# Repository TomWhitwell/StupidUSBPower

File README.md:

# StupidUSBPower

This is a USB Stick Eurorack Power supply. 

- It takes +5v from USB power, and turns it into +/-12v and also passes along the 5v. 
- The key component is a IR0512S DC-DC Converter from XP Power which [costs about £8.50 from Farnell](http://uk.farnell.com/xp-power/ir0512s/dc-dc-converter-semi-reg-dual/dp/1860988) and gives 125mA of power on both rails.  This is a standard SIP package, so other dual output DC-DC converters may work in the same spot. I just chose the one with a good output. 
- The board also includes a simple passive headphone output; the 3.5mm mono socket goes through a 50k Volume Pot into the stereo headphone socket. This didn't work well with three-connector iphone earbuds, but was fine with normal stereo headphones. 
- Seems to work well with portable USB batteries. 
- The IR0512S is rated 125mA on +12v and -12v, but that seems quite conservative. The Dixie+Turing+Radio Music in the photo below ran quite happily, with an expected current draw of 160mA on +12v, 52mA on -12v. The converter module was warm but certainly not hot. The whole thing was drawing 600mA from the USB port. 

## Updates 
- This project has taken off a little bit! [C1T1ZEN](https://www.instagram.com/p/BEDGNGCOpEv/?taken-by=c1t1zen) has been building incredibly cool lunchbox euro boxes powered with his improved version. 
- Just got a [Re:Load2](http://www.arachnidlabs.com/reload-2/) so I've been trying to destroy my USB power prototype. With the IR0512S...
    - 250ma on +12v: Seems to work quite happily, pulling 710ma from the USB port. 
    - 350ma: It appears to work OK. The lights are on, but I'm making no no claims on the power stability, ripple etc, pulling about 1amp from USB, the converter is definitely HOT, but ran for an afternoon without death. 
    - 460ma: Seems to be the absolute max. Really hot. Above that, when you try to pull more current, all the lights blink and it says goodbye. The IR0512S seems to have an internal fuse, so recovers after it's cooled down. So: no actual magic smoke but definitely some warm plastic smells.
    - I initially had a 1a Polyfuse on the USB line (short circuited for this test) - that certainly seems sensible in the light of this - maybe 750ma would be safer.  
    - Conclusions: This was a raw test: power to load, so can't draw any conclusions about what makes a good/stable/safe PSU for your modules, but it explains why I was able to power more than 125ma worth of modules with this thing.  

## Reasons why this is stupid: 

3. There are no fuses or protection devices anywhere in the circuit. If you plug this plus $800 worth of modules into a $2000 laptop, you're taking a risk. NB: Do not do this. 
4. There is no filtering in the system, so there will be clock noise from the converter on the rails. The datasheet and my measurements suggest it's in the 60-85khz range. Do not use this to play live or record your new album. 
2. 125mA isn't very much power. Just because the module seems to run above that rating doesn't mean it's safe or reliable.  
1. Designing this as a memory stick is conceptually strong, but it would be much safer and easier to use with a female USB socket and a short cable.
2. Keyed headers are not reverse power protection. 
 
## Status 
- Eagle files and Gerbers (optimised for [OSH Park](https://oshpark.com/)) are in this repository. 
- These are Rev1.1 boards. The prototype below is Rev 1, which had the -12v LED reversed and needed a bit of trimming to get the USB socket on. I haven't built any 1.1 boards, but I'd be very confident that they'll work. 
- This project is Creative Commmons Licensed [CC-BY-SA](https://creativecommons.org/licenses/by-sa/3.0/). If you like the idea, why not develop it a little and submit your changes here? 
- I haven't exported a formal BOM. The only non-obvious bits aside from the DC-DC converter are: 
    - [USB Socket Type A, Through Hole](http://uk.farnell.com/multicomp/mc32603/usb-2-0-type-a-plug-th/dp/1696544)  
    - [Lumberg  150309 Stereo Socket](http://uk.farnell.com/lumberg/1503-09/connector-rca-jack-3-5mm-3way/dp/1243244)
    - [Amphenol  T821116A1S100CEU  Shrouded headers](http://uk.farnell.com/amphenol/t821116a1s100ceu/header-vertical-2-54mm-16way/dp/2215308)  
    - [Thonkiconn](http://www.thonk.co.uk/shop/thonkiconn-3-5mm-jack-sockets-x50/) mono jack socket, [Alpha](http://www.thonk.co.uk/shop/ttpots/) Pot, 3mm LEDs, 2k LED Resistors, 47uF 16v capacitor on the 5v line.

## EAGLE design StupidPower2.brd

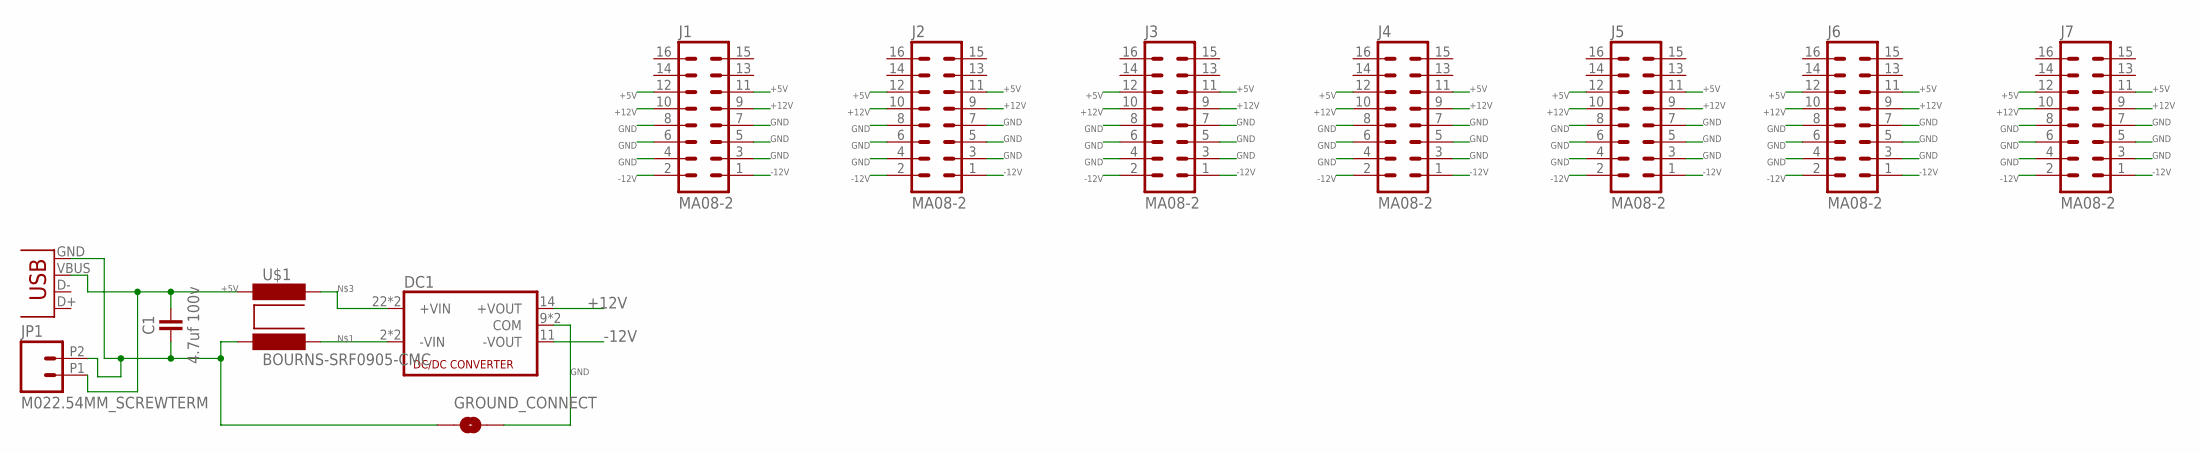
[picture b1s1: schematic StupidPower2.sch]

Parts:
C1: 4.7uf 100v; C1206
DC1: XPOWER-JCA; XP-POWER_JCA
GROUND_CONNECT: SOLDERJUMPERNO; SJ_2S-NO
J1, J2, J3, J4, J5, J6, J7: MA08-2
JP1: M022.54MM_SCREWTERM; 1X02_2.54_SCREWTERM
JP2: USB-B; USB-B-PTH
U$1: BOURNS-SRF0905-CMC; BOURNS-SRF0905-LINEFILTER

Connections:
+5V: C1.2, J1.11, J1.12, J2.11, J2.12, J3.11, J3.12, J4.11, J4.12, J5.11, J5.12, J6.11, J6.12, J7.11, J7.12, JP1.P1 (1), JP2.VBUS, U$1.2
+12V: DC1.14 (+VOUT), J1.9, J1.10, J2.9, J2.10, J3.9, J3.10, J4.9, J4.10, J5.9, J5.10, J6.9, J6.10, J7.9, J7.10
-12V: DC1.11 (-VOUT), J1.1, J1.2, J2.1, J2.2, J3.1, J3.2, J4.1, J4.2, J5.1, J5.2, J6.1, J6.2, J7.1, J7.2
GND: DC1.9 (COM), DC1.16 (COM), GROUND_CONNECT.2, J1.3, J1.4, J1.5, J1.6, J1.7, J1.8, J2.3, J2.4, J2.5, J2.6, J2.7, J2.8, J3.3, J3.4, J3.5, J3.6, J3.7, J3.8, J4.3, J4.4, J4.5, J4.6, J4.7, J4.8, J5.3, J5.4, J5.5, J5.6, J5.7, J5.8, J6.3, J6.4, J6.5, J6.6, J6.7, J6.8, J7.3, J7.4, J7.5, J7.6, J7.7, J7.8
GND_INLET: C1.1, GROUND_CONNECT.1, JP1.P2 (2), JP2.GND, U$1.1
unnamed: DC1.2 (-VIN), DC1.3 (-VIN), U$1.4
unnamed: DC1.22 (+VIN), DC1.23 (+VIN), U$1.3

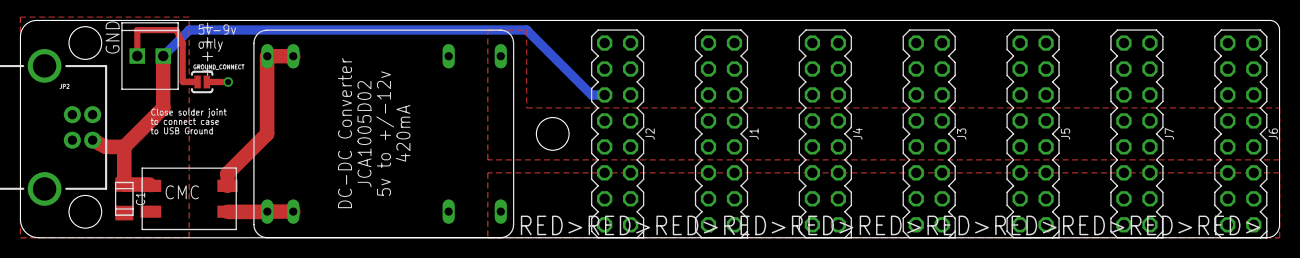
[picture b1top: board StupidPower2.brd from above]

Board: 2 copper layers, 123.2 x 21.3 mm, 13 parts (0 on the bottom side), 7 nets.

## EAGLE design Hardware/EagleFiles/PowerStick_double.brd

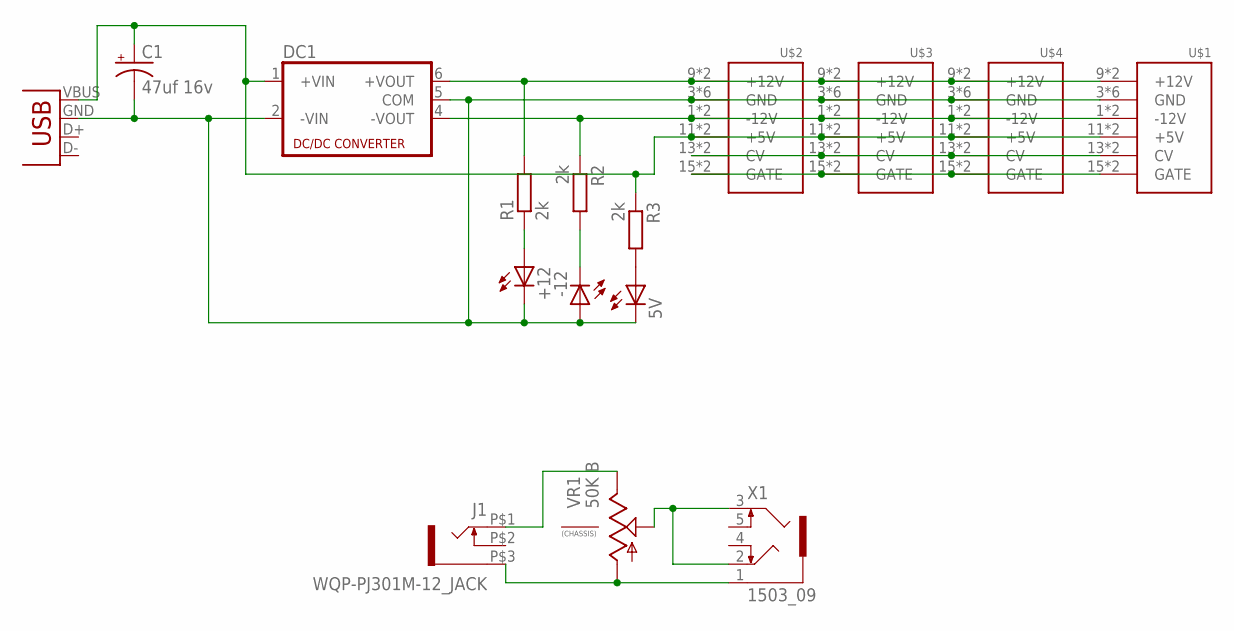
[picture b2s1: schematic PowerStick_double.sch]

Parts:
5V: LED3MM
+12: LED3MM
-12: LED3MM
C1: 47uf 16v; 050_020
DC1: NMA
J1: WQP-PJ301M-12_JACK
JP1: USB-A-H
R1, R2, R3: 2k; 7MM_RESISTOR
U$1, U$2, U$3, U$4: POWER; POWER_16
VR1: 50K B; 9MM_SNAP-IN_POT
X1: 1503_09

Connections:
5V: C1.+, DC1.1 (+VIN), JP1.VBUS (GND), R3.1, U$1.11 (+5V), U$1.12 (+5V), U$2.11 (+5V), U$2.12 (+5V), U$3.11 (+5V), U$3.12 (+5V), U$4.11 (+5V), U$4.12 (+5V)
+12V: DC1.6 (+VOUT), R1.2, U$1.9 (+12V), U$1.10 (+12V), U$2.9 (+12V), U$2.10 (+12V), U$3.9 (+12V), U$3.10 (+12V), U$4.9 (+12V), U$4.10 (+12V)
-12V: DC1.4 (-VOUT), R2.1, U$1.1 (-12V), U$1.2 (-12V), U$2.1 (-12V), U$2.2 (-12V), U$3.1 (-12V), U$3.2 (-12V), U$4.1 (-12V), U$4.2 (-12V)
COM: 5V.K (C), +12.K (C), -12.A, C1.-, DC1.2 (-VIN), DC1.5 (COM), J1.P$3 (1), JP1.GND (VBUS), U$1.3 (GND), U$1.4 (GND), U$1.5 (GND), U$1.6 (GND), U$1.7 (GND), U$1.8 (GND), U$2.3 (GND), U$2.4 (GND), U$2.5 (GND), U$2.6 (GND), U$2.7 (GND), U$2.8 (GND), U$3.3 (GND), U$3.4 (GND), U$3.5 (GND), U$3.6 (GND), U$3.7 (GND), U$3.8 (GND), U$4.3 (GND), U$4.4 (GND), U$4.5 (GND), U$4.6 (GND), U$4.7 (GND), U$4.8 (GND), VR1.1 (A), X1.1
unnamed: -12.K (C), R2.2
unnamed: U$1.13 (CV), U$1.14 (CV), U$2.13 (CV), U$2.14 (CV), U$3.13 (CV), U$3.14 (CV), U$4.13 (CV), U$4.14 (CV)
unnamed: U$1.15 (GATE), U$1.16 (GATE), U$2.15 (GATE), U$2.16 (GATE), U$3.15 (GATE), U$3.16 (GATE), U$4.15 (GATE), U$4.16 (GATE)
unnamed: 5V.A, R3.2
unnamed: +12.A, R1.1
unnamed: J1.P$1 (2), VR1.3 (E)
unnamed: VR1.2 (S), X1.2, X1.3

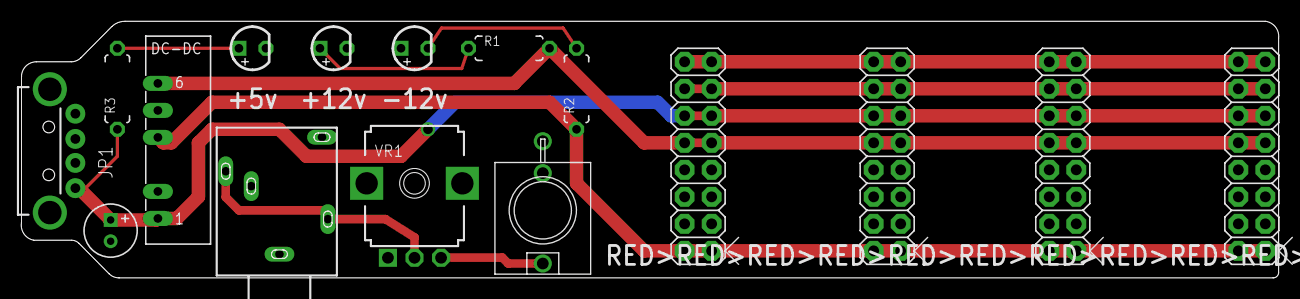
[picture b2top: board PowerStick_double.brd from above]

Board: 4 copper layers, 118.2 x 24.1 mm, 16 parts (0 on the bottom side), 11 nets.

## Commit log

2015-08-03 Upload rev1.1 Eagle & Gerber files
    Rev1 was prototyped, this version flips polarity of the -12v LED (doh),
    skims off a bit of PCB edge next to the USB connector and moves the
    stereo jack slightly closer to the PCB edge.
2015-08-03 images + folders
2018-04-12 Rev2_NOT WORKING!

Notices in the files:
parts and their libraries:
SparkFun-Connectors: Licensing: CC v3.0 Share-Alike You are welcome to use this library for commercial purposes.
